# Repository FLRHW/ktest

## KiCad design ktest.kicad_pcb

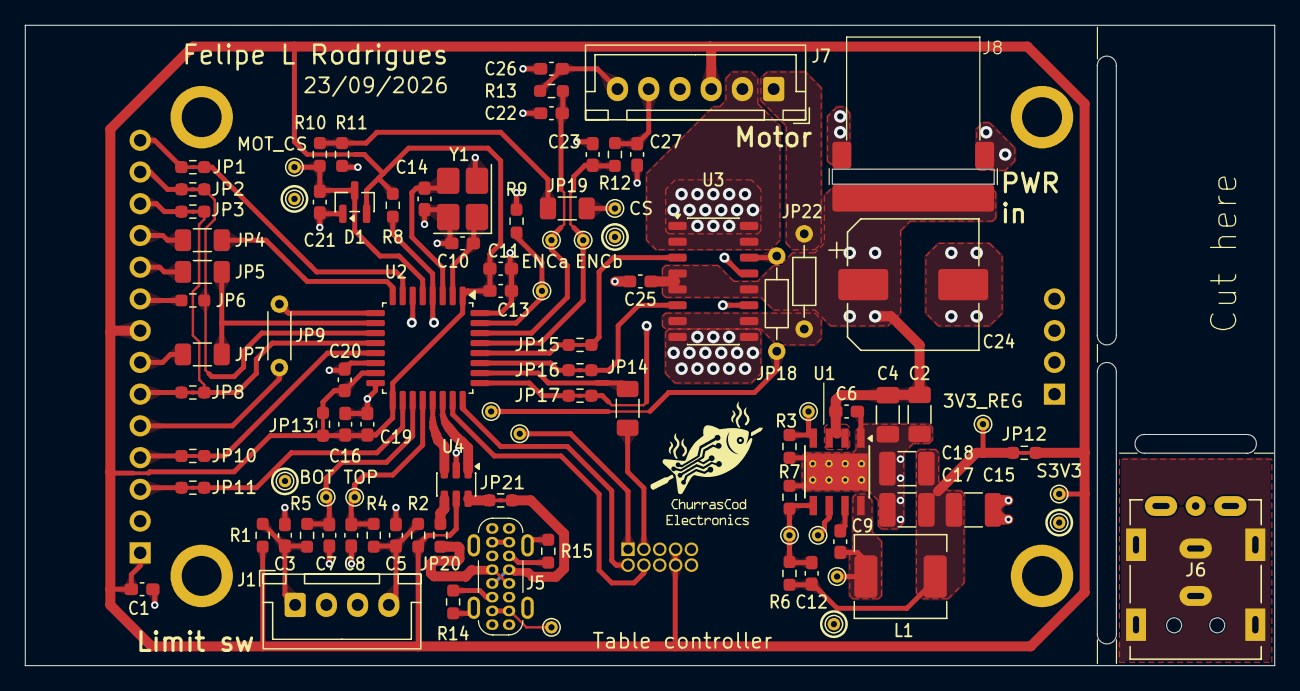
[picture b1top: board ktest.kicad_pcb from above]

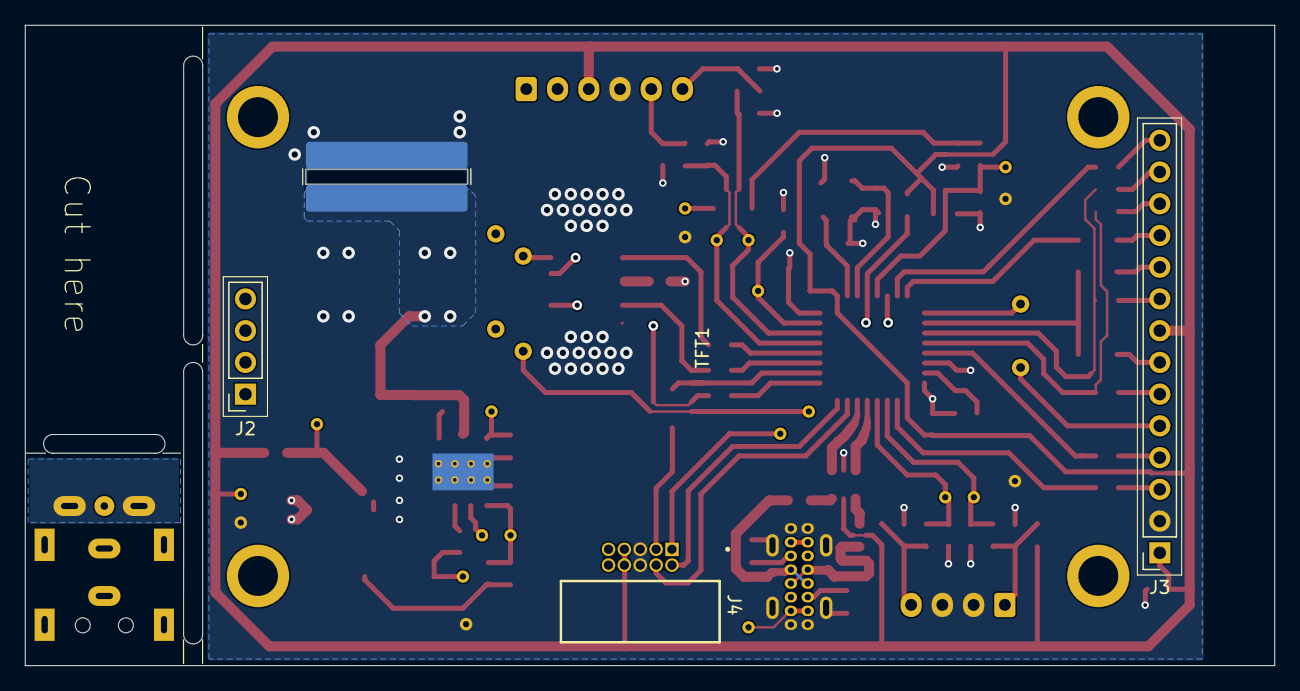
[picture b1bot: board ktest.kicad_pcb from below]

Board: 4 copper layers, 100.0 x 51.2 mm, 101 parts (4 on the bottom side), 69 nets.

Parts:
C1, C6, C9, C13, C19, C20, C25: 100n; C_0603_1608Metric_Pad1.08x0.95mm_HandSolder
C2, C4: 4.7u; C_1206_3216Metric_Pad1.33x1.80mm_HandSolder
C3, C5, C26, C27: 10n; C_0603_1608Metric_Pad1.08x0.95mm_HandSolder
C7, C8, C21, C22, C23: 1n; C_0603_1608Metric_Pad1.08x0.95mm_HandSolder
C10, C14: 22p; C_0603_1608Metric_Pad1.08x0.95mm_HandSolder
C11, C16: 1u; C_0603_1608Metric_Pad1.08x0.95mm_HandSolder
C12: 33p; C_0603_1608Metric_Pad1.08x0.95mm_HandSolder
C15, C17, C18: 22u; C_1210_3225Metric_Pad1.33x2.70mm_HandSolder
C24: 220u; CP_Elec_10x10
D1: BAV99; SOT-23
J1: B4B XH A; JST_XH_B4B-XH-A_1x04_P2.50mm_Vertical
J2: 01x04 socket; PinSocket_1x04_P2.54mm_Vertical
J3: 01x14 socket; PinSocket_1x14_P2.54mm_Vertical
J4: HX JN1.27-2x5 WZ H4.9; JN1.27-2x5 WZ H4.9
J5: USB_C_Receptacle_USB2.0_16P; USB_C_socket_16P_vertical
J6: Dell DC jack
J7: B6B XH A; JST_XH_B6B-XH-A_1x06_P2.50mm_Vertical
J8: DC barrel assy; Dell_barrel_assy
JP1, JP2, JP3, JP8, JP10, JP11, JP12, JP13, JP15, JP16, JP17, JP21: 0R; Jumper_0603
JP4, JP5, JP7, JP14, JP19: 0R; R_1206_3216Metric_Pad1.30x1.75mm_HandSolder
JP6, JP20: 0R; R_0603_1608Metric_Pad0.98x0.95mm_HandSolder
JP9: 0R; R_Axial_DIN0204_L3.6mm_D1.6mm_P5.08mm_Horizontal
JP18, JP22: 0R; R_Axial_DIN0204_L3.6mm_D1.6mm_P7.62mm_Horizontal
L1: 10u; L_Bourns_SRP6540
R1, R2, R7, R8, R9: 10k; R_0603_1608Metric_Pad0.98x0.95mm_HandSolder
R3: 64.9k; R_0603_1608Metric_Pad0.98x0.95mm_HandSolder
R4, R5, R10, R12, R13: 2k2; R_0603_1608Metric_Pad0.98x0.95mm_HandSolder
R6: 23.2k; R_0603_1608Metric_Pad0.98x0.95mm_HandSolder
R11: 820; R_0603_1608Metric_Pad0.98x0.95mm_HandSolder
R14, R15: 5k1; R_0603_1608Metric_Pad0.98x0.95mm_HandSolder
TFT1: TFT_2.4in_320x240; Display_240x320_ILI9341_2.4in_no_pads
TP1, TP2, TP3, TP4, TP5, TP6, TP7, TP8, TP9, TP10, TP11, TP12, TP13, TP14, TP15, TP16, TP17, TP18, TP19, TP20, TP21: TestPoint; TestPoint_THTPad_D1.0mm_Drill0.5mm
U1: LMR38020; Texas_HSOP-8-1EP_3.9x4.9mm_P1.27mm_ThermalVias
U2: STM32G431K8T; LQFP-32_7x7mm_P0.8mm
U3: VNH7070; JEITA_SOIC-16_3.9x9.9mm_P1.27mm
U4: USBLC6-2SC6; SOT-23-6
Y1: 20 MHz; Crystal_SMD_3225-4Pin_3.2x2.5mm_HandSoldering

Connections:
/System overview/Block diagram/DCDC converter 3V3/3V3_REG: C12.1, C15.1, C17.1, C18.1, JP12.1, L1.2, R6.1, TP10.1 (1_1)
/System overview/Block diagram/DCDC converter 3V3/FB: C12.2, R6.2, R7.1, TP5.1 (1_1), U1.5 (FB)
/System overview/Block diagram/DCDC converter 3V3/GND_2: J6.3 (-), J6.SH
/System overview/Block diagram/DCDC converter 3V3/PG: TP1.1 (1_1), U1.6 (PG)
/System overview/Block diagram/DCDC converter 3V3/RT: R3.1, TP2.1 (1_1), U1.4 (RT/SYNC)
/System overview/Block diagram/DCDC converter 3V3/SW: C9.2, L1.1, TP6.1 (1_1), U1.8 (SW)
/System overview/Block diagram/Display/DISP_CS: JP11.1, U2.18 (PA8)
/System overview/Block diagram/Display/DISP_DC: JP9.1, U2.9 (PA4)
/System overview/Block diagram/Display/DISP_MISO: JP2.1, JP6.1, U2.11 (PA6)
/System overview/Block diagram/Display/DISP_MOSI: JP3.1, JP8.1, U2.12 (PA7)
/System overview/Block diagram/Display/DISP_RST: JP10.1, U2.13 (PB0)
/System overview/Block diagram/Display/DISP_SCK: JP5.1, JP7.1, U2.10 (PA5)
/System overview/Block diagram/Display/TCH_CS: JP4.1, U2.8 (PA3)
/System overview/Block diagram/Display/TCH_IRQ: JP1.1, U2.7 (PA2)
/System overview/Block diagram/GND: C1.2, C2.2, C3.2, C4.2, C5.2, C6.2, C7.2, C8.2, C10.2, C11.2, C13.2, C14.2, C15.2, C16.2, C17.2, C18.2, C19.2, C20.2, C21.2, C22.2, C23.2, C24.2, C25.2, C26.2, C27.2, D1.1 (K), J1.2, J1.3, J3.2, J4.5, J4.6, J5.A1 (GND), J5.A12 (GND), J5.B1 (GND), J5.B12 (GND), J5.SH (SHIELD), J7.4, J8.2 (-), R3.2, R7.2, R9.2, R11.2, R14.2, R15.2, TP7.1 (1_1), TP18.1 (1_1), TP19.1 (1_1), TP20.1 (1_1), TP21.1 (1_1), U1.1 (GND), U1.9 (EP), U2.14 (VSSA), U2.16 (VSS), U2.32 (VSS), U3.1 (GNDa), U3.8 (GNDb), U3.9 (GNDb), U3.16 (GNDa), U4.2 (GND), Y1.2 (G), Y1.4 (G)
/System overview/Block diagram/Limit switch interface/BOT_EOT: C3.1, J1.1, R1.2, R5.1
/System overview/Block diagram/Limit switch interface/BOT_filt: C7.1, R5.2, TP4.1 (1_1), U2.19 (PA9)
/System overview/Block diagram/Limit switch interface/TOP_EOT: C5.1, J1.4, R2.2, R4.1
/System overview/Block diagram/Limit switch interface/TOP_filt: C8.1, R4.2, TP3.1 (1_1), U2.20 (PA10)
/System overview/Block diagram/Microcontroller/BOOT0: R9.1, TP9.1 (1_1), U2.31 (PB8)
/System overview/Block diagram/Microcontroller/CC1: J5.A5 (CC1), R14.1
/System overview/Block diagram/Microcontroller/CC2: J5.B5 (CC2), R15.1
/System overview/Block diagram/Microcontroller/D+: J5.A6 (D+), J5.B6 (D+), JP21.1
/System overview/Block diagram/Microcontroller/D+': JP21.2, U4.6 (I/O1)
/System overview/Block diagram/Microcontroller/D-: J5.A7 (D-), J5.B7 (D-), JP20.1
/System overview/Block diagram/Microcontroller/D-': JP20.2, U4.4 (I/O2)
/System overview/Block diagram/Microcontroller/ENCa_filt: C23.1, R12.1, TP12.1 (1_1), U2.29 (PB6)
/System overview/Block diagram/Microcontroller/ENCb_filt: C22.1, R13.1, TP13.1 (1_1), U2.30 (PB7)
/System overview/Block diagram/Microcontroller/INa: JP15.1, U2.28 (PB5)
/System overview/Block diagram/Microcontroller/INb: JP16.1, U2.27 (PB4)
/System overview/Block diagram/Microcontroller/MOT_CS: C21.1, D1.3 (K), R10.1, TP14.1 (1_1), U2.5 (PA0)
/System overview/Block diagram/Microcontroller/NRST: J4.1, R8.2, TP8.1 (1_1), U2.4 (PG10)
/System overview/Block diagram/Microcontroller/PWM: JP17.1, U2.25 (PA15)
/System overview/Block diagram/Microcontroller/S3V3_A: C20.1, JP13.2, U2.15 (VDDA)
/System overview/Block diagram/Microcontroller/SEL0: JP18.2, TP11.1 (1_1), U2.6 (PA1)
/System overview/Block diagram/Microcontroller/SWDCLK: J4.2, U2.24 (PA14)
/System overview/Block diagram/Microcontroller/SWDIO: J4.4, U2.23 (PA13)
/System overview/Block diagram/Microcontroller/SWO: JP14.1, U2.26 (PB3)
/System overview/Block diagram/Microcontroller/SWO': J4.3, JP14.2
/System overview/Block diagram/Microcontroller/USB_DM: U2.21 (PA11), U4.3 (I/O2)
/System overview/Block diagram/Microcontroller/USB_DP: U2.22 (PA12), U4.1 (I/O1)
/System overview/Block diagram/Microcontroller/XIN: C10.1, U2.2 (PF0), Y1.1
/System overview/Block diagram/Microcontroller/XOUT: C14.1, U2.3 (PF1), Y1.3
/System overview/Block diagram/S3V3: C1.1, C11.1, C13.1, C16.1, C19.1, D1.2 (A), J3.1, J3.8, J4.7, J4.8, J7.3, JP12.2, JP13.1, R1.1, R2.1, R8.1, TP17.1 (1_1), U2.1 (VDD), U2.17 (VDD), U4.5 (VBUS)
/System overview/Block diagram/S19V5: C2.1, C4.1, C6.1, C24.1, C25.1, J8.1 (+), U1.2 (EN), U1.3 (VIN), U3.4 (VCC), U3.5 (VCC), U3.12 (VCC)
/System overview/Block diagram/Servomotor interface/CS': JP19.2, TP15.1 (1_1), U3.13 (CS)
/System overview/Block diagram/Servomotor interface/ENCa: C27.1, J7.5, R12.2
/System overview/Block diagram/Servomotor interface/ENCb: C26.1, J7.6, R13.2
/System overview/Block diagram/Servomotor interface/INa': JP15.2, U3.3 (INa)
/System overview/Block diagram/Servomotor interface/INb': JP16.2, U3.6 (INb)
/System overview/Block diagram/Servomotor interface/OUTa: J7.2, U3.2 (OUTa), U3.15 (OUTa)
/System overview/Block diagram/Servomotor interface/OUTb: J7.1, JP22.1
/System overview/Block diagram/Servomotor interface/OUTb': JP22.2, U3.7 (OUTb), U3.10 (OUTb)
/System overview/Block diagram/Servomotor interface/PWM': JP17.2, U3.11 (PWM)
/System overview/Block diagram/Servomotor interface/SEL0': JP18.1, U3.14 (SEL0)
unnamed: J3.3, JP11.2
unnamed: J3.4, JP10.2
unnamed: J3.5, JP9.2
unnamed: J3.6, JP8.2
unnamed: J3.7, JP7.2
unnamed: J3.9, JP6.2
unnamed: J3.10, JP5.2
unnamed: J3.11, JP4.2
unnamed: J3.12, JP3.2
unnamed: J3.13, JP2.2
unnamed: J3.14, JP1.2
unnamed: J5.A4 (VBUS), J5.A9 (VBUS), J5.B4 (VBUS), J5.B9 (VBUS), TP16.1 (1_1)
unnamed: JP19.1, R10.2, R11.1
unnamed: C9.1, U1.7 (BOOT)

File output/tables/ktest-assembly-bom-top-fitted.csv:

References,Qty,Value,Footprint,MPN,Manufacturer,Status
C1 C6 C9 C13 C19 C20 C25,7,100n,C_0603_1608Metric_Pad1.08x0.95mm_HandSolder,AC0603KRX7R9BB104,Yageo, 
C3 C5 C26 C27,4,10n,C_0603_1608Metric_Pad1.08x0.95mm_HandSolder,AC0603KRX7R9BB103,Yageo, 
C7 C8 C21 C22 C23,5,1n,C_0603_1608Metric_Pad1.08x0.95mm_HandSolder,AC0603KRX7R9BB102,Yageo, 
C11 C16,2,1u,C_0603_1608Metric_Pad1.08x0.95mm_HandSolder,AC0603KRX7R7BB105,Yageo, 
C24,1,220u,CP_Elec_10x10,EEE-FK1H221P,Panasonic, 
C10 C14,2,22p,C_0603_1608Metric_Pad1.08x0.95mm_HandSolder,AC0603JRNPO9BN220,Yageo, 
C15 C17 C18,3,22u,C_1210_3225Metric_Pad1.33x2.70mm_HandSolder,MCAST32MSB7226KPNA01,TAIYO YUDEN, 
C12,1,33p,C_0603_1608Metric_Pad1.08x0.95mm_HandSolder,AC0603JRNPO9BN330,Yageo, 
C2 C4,2,4.7u,C_1206_3216Metric_Pad1.33x1.80mm_HandSolder,C1206C475K5RACAUTO,KEMET, 
D1,1,BAV99,SOT-23,BAV99Q-7-F,Diodes Inc, 
J1,1,B4B XH A,JST_XH_B4B-XH-A_1x04_P2.50mm_Vertical,B4B XH A,JST, 
J7,1,B6B XH A,JST_XH_B6B-XH-A_1x06_P2.50mm_Vertical,B6B XH A,JST, 
J8,1,DC barrel assy,Dell_barrel_assy,NA,NA, 
J6,1,Dell DC jack,Dell DC jack,Barrel jack,Dell, 
J5,1,USB_C_Receptacle_USB2.0_16P,USB_C_socket_16P_vertical,TFKH5-16L4CC-65,ChengHaoRan, 
JP4 JP5 JP7 JP14 JP19,5,0R,R_1206_3216Metric_Pad1.30x1.75mm_HandSolder,Hand cut wire,Generic, 
JP18 JP22,2,0R,R_Axial_DIN0204_L3.6mm_D1.6mm_P7.62mm_Horizontal,Hand cut wire,Generic, 
JP6 JP20,2,0R,R_0603_1608Metric_Pad0.98x0.95mm_HandSolder,RC0603JR-130RP,Yageo, 
JP9,1,0R,R_Axial_DIN0204_L3.6mm_D1.6mm_P5.08mm_Horizontal,Hand cut wire,Generic, 
L1,1,10u,L_Bourns_SRP6540,SRP6540-100M,Bourns, 
R1 R2 R7 R8 R9,5,10k,R_0603_1608Metric_Pad0.98x0.95mm_HandSolder,AC0603FR-0710KL,YAGEO, 
R6,1,23.2k,R_0603_1608Metric_Pad0.98x0.95mm_HandSolder,AC0603FR-0723K2L,YAGEO, 
R4 R5 R10 R12 R13,5,2k2,R_0603_1608Metric_Pad0.98x0.95mm_HandSolder,AC0603FR-072K2L,YAGEO, 
R14 R15,2,5k1,R_0603_1608Metric_Pad0.98x0.95mm_HandSolder,AC0603FR-075K1L,YAGEO, 
R3,1,64.9k,R_0603_1608Metric_Pad0.98x0.95mm_HandSolder,AC0603FR-0764K9L,YAGEO, 
R11,1,820,R_0603_1608Metric_Pad0.98x0.95mm_HandSolder,AC0603FR-07820RL,YAGEO, 
U1,1,LMR38020,Texas_HSOP-8-1EP_3.9x4.9mm_P1.27mm_ThermalVias,LMR38020FDDAR,Texas instruments, 
U2,1,STM32G431K8T,LQFP-32_7x7mm_P0.8mm,STM32G431K8T6,ST, 
U4,1,USBLC6-2SC6,SOT-23-6,USBLC6-2SC6,ST, 
U3,1,VNH7070,JEITA_SOIC-16_3.9x9.9mm_P1.27mm,VNH7070,ST, 
Y1,1,20 MHz,Crystal_SMD_3225-4Pin_3.2x2.5mm_HandSoldering,CX3225SB20000H0FLJCC,KYOCERA AVX,
